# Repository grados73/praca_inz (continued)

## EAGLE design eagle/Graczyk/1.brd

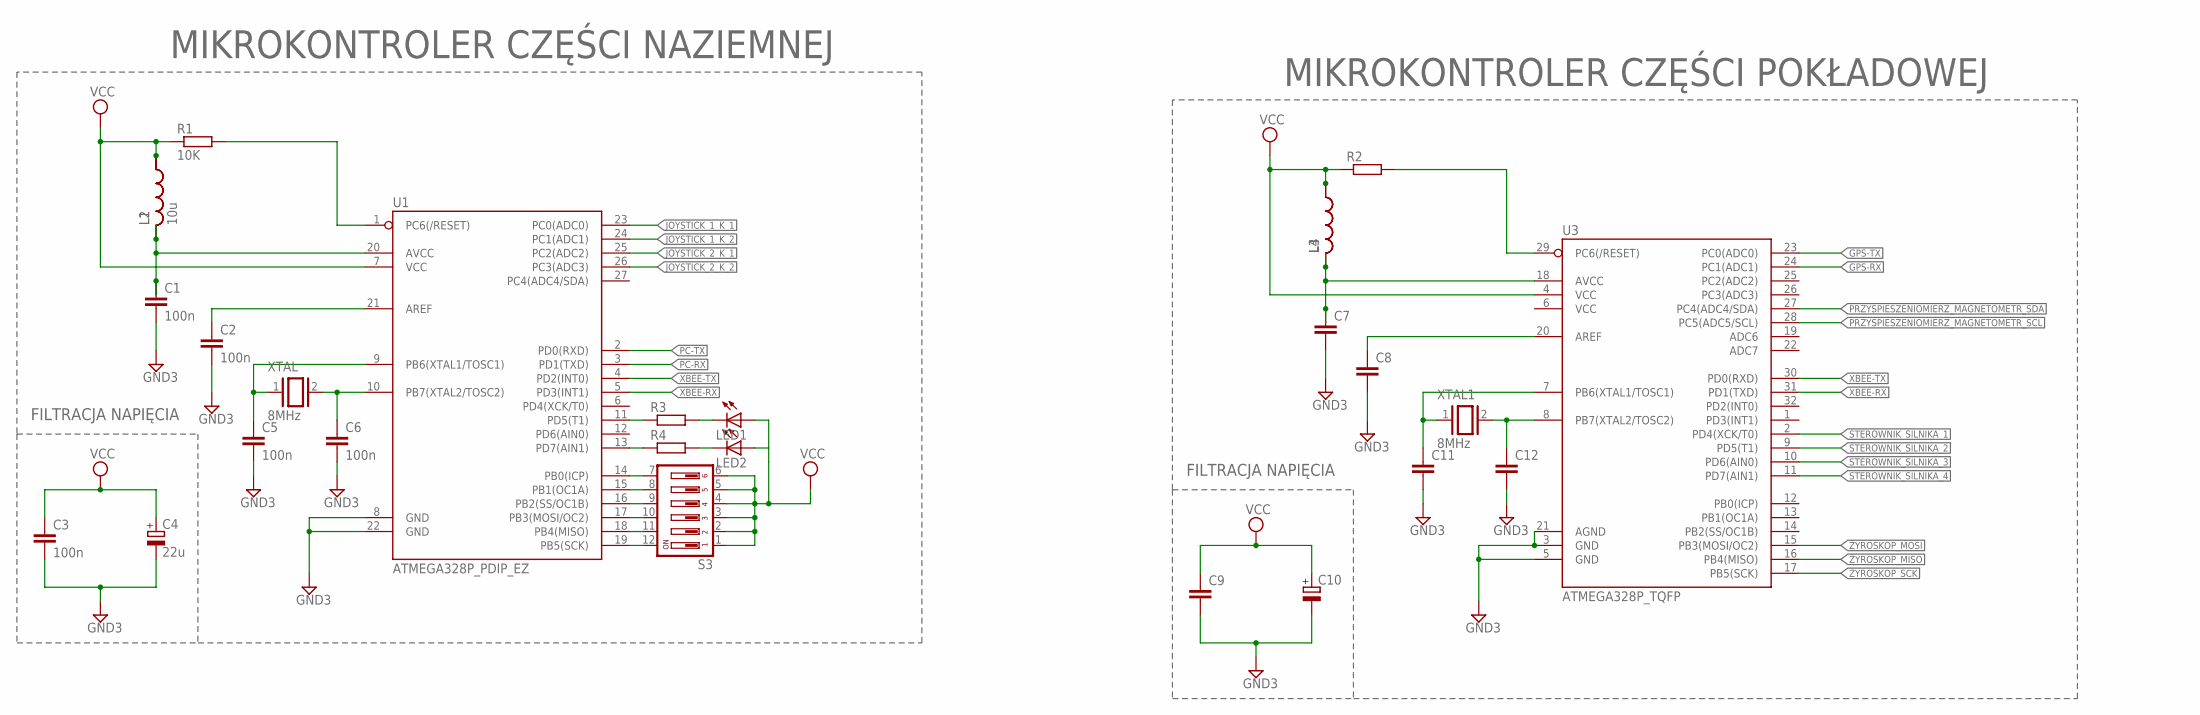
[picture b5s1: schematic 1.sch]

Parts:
C1, C2, C3, C5, C6: 100n; C050-025X075
C4: 22u; B45181A
C7, C8, C9, C11, C12: C-EU050-025X075; C050-025X075
C10: CPOL-EUB45181A; B45181A
L1, L3, L4: L-US0207/10; 0207/10
L2: 10u; 0207/10
LED1, LED2: LEDIRL80A; IRL80A
R1: 10K; 0204/5
R2, R3, R4: R-EU_0204/5; 0204/5
S3: SD4-06
U1: ATMEGA328P_PDIP_EZ; DIP28-SIMON-KIT
U3: ATMEGA328P_TQFP; TQFP32-08
XTAL, XTAL1: 8MHz; Q

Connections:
GND3: C1.2, C2.2, C3.2, C4.-, C5.2, C6.2, C7.2, C8.2, C9.2, C10.-, C11.2, C12.2, U1.8 (GND), U1.22 (GND), U3.3 (GND), U3.5 (GND), U3.21 (AGND)
GPS-RX: U3.24 (PC1(ADC1))
GPS-TX: U3.23 (PC0(ADC0))
JOYSTICK_1_K_1: U1.23 (PC0(ADC0))
JOYSTICK_1_K_2: U1.24 (PC1(ADC1))
JOYSTICK_2_K_1: U1.25 (PC2(ADC2))
JOYSTICK_2_K_2: U1.26 (PC3(ADC3))
unnamed: R1.2, U1.1 (PC6(/RESET))
unnamed: C1.1, L1.2, L2.2, U1.20 (AVCC)
unnamed: C2.1, U1.21 (AREF)
unnamed: R2.2, U3.29 (PC6(/RESET))
unnamed: C6.1, U1.10 (PB7(XTAL2/TOSC2)), XTAL.2
unnamed: C5.1, U1.9 (PB6(XTAL1/TOSC1)), XTAL.1
unnamed: C7.1, L3.2, L4.2, U3.18 (AVCC)
unnamed: C8.1, U3.20 (AREF)
unnamed: C12.1, U3.8 (PB7(XTAL2/TOSC2)), XTAL1.2
unnamed: C11.1, U3.7 (PB6(XTAL1/TOSC1)), XTAL1.1
unnamed: LED1.K (C), R3.2
unnamed: S3.7, U1.14 (PB0(ICP))
unnamed: S3.8, U1.15 (PB1(OC1A))
unnamed: S3.9, U1.16 (PB2(SS/OC1B))
unnamed: S3.10, U1.17 (PB3(MOSI/OC2))
unnamed: S3.11, U1.18 (PB4(MISO))
unnamed: S3.12, U1.19 (PB5(SCK))
unnamed: LED2.K (C), R4.2
unnamed: R4.1, U1.13 (PD7(AIN1))
unnamed: R3.1, U1.11 (PD5(T1))
PRZYSPIESZENIOMIERZ_MAGNETOMETR_SCL: U3.28 (PC5(ADC5/SCL))
PRZYSPIESZENIOMIERZ_MAGNETOMETR_SDA: U3.27 (PC4(ADC4/SDA))
STEROWNIK_SILNIKA_1: U3.2 (PD4(XCK/T0))
STEROWNIK_SILNIKA_2: U3.9 (PD5(T1))
STEROWNIK_SILNIKA_3: U3.10 (PD6(AIN0))
STEROWNIK_SILNIKA_4: U3.11 (PD7(AIN1))
VCC: C3.1, C4.+, C9.1, C10.+, L1.1, L2.1, L3.1, L4.1, LED1.A, LED2.A, R1.1, R2.1, S3.1, S3.2, S3.3, S3.4, S3.5, S3.6, U1.7 (VCC), U3.4 (VCC)
XBEE-RX: U3.31 (PD1(TXD))
XBEE-TX: U3.30 (PD0(RXD))
ŻYROSKOP_MISO: U3.16 (PB4(MISO))
ŻYROSKOP_MOSI: U3.15 (PB3(MOSI/OC2))
ŻYROSKOP_SCK: U3.17 (PB5(SCK))

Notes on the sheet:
MIKROKONTROLER CZĘŚCI NAZIEMNEJ
MIKROKONTROLER CZĘŚCI POKŁADOWEJ
FILTRACJA NAPIĘCIA

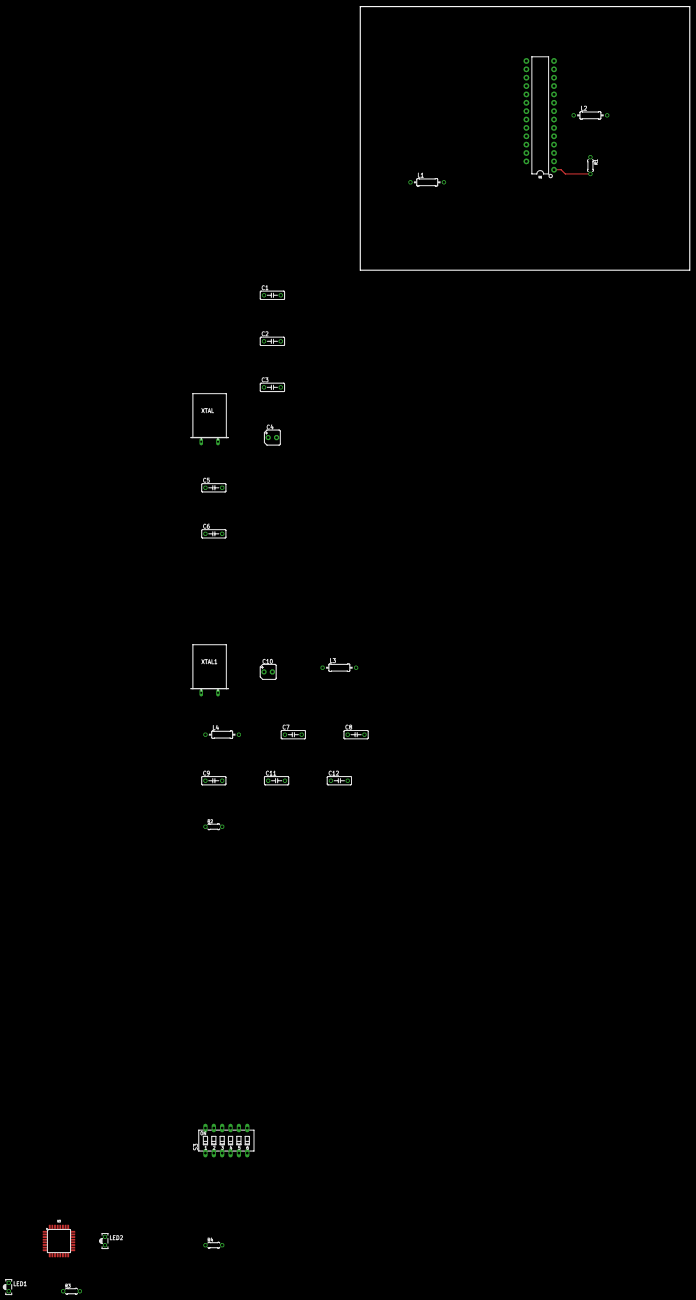
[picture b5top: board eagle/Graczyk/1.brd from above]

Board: 2 copper layers, 100.0 x 80.0 mm, 27 parts (0 on the bottom side), 22 nets.

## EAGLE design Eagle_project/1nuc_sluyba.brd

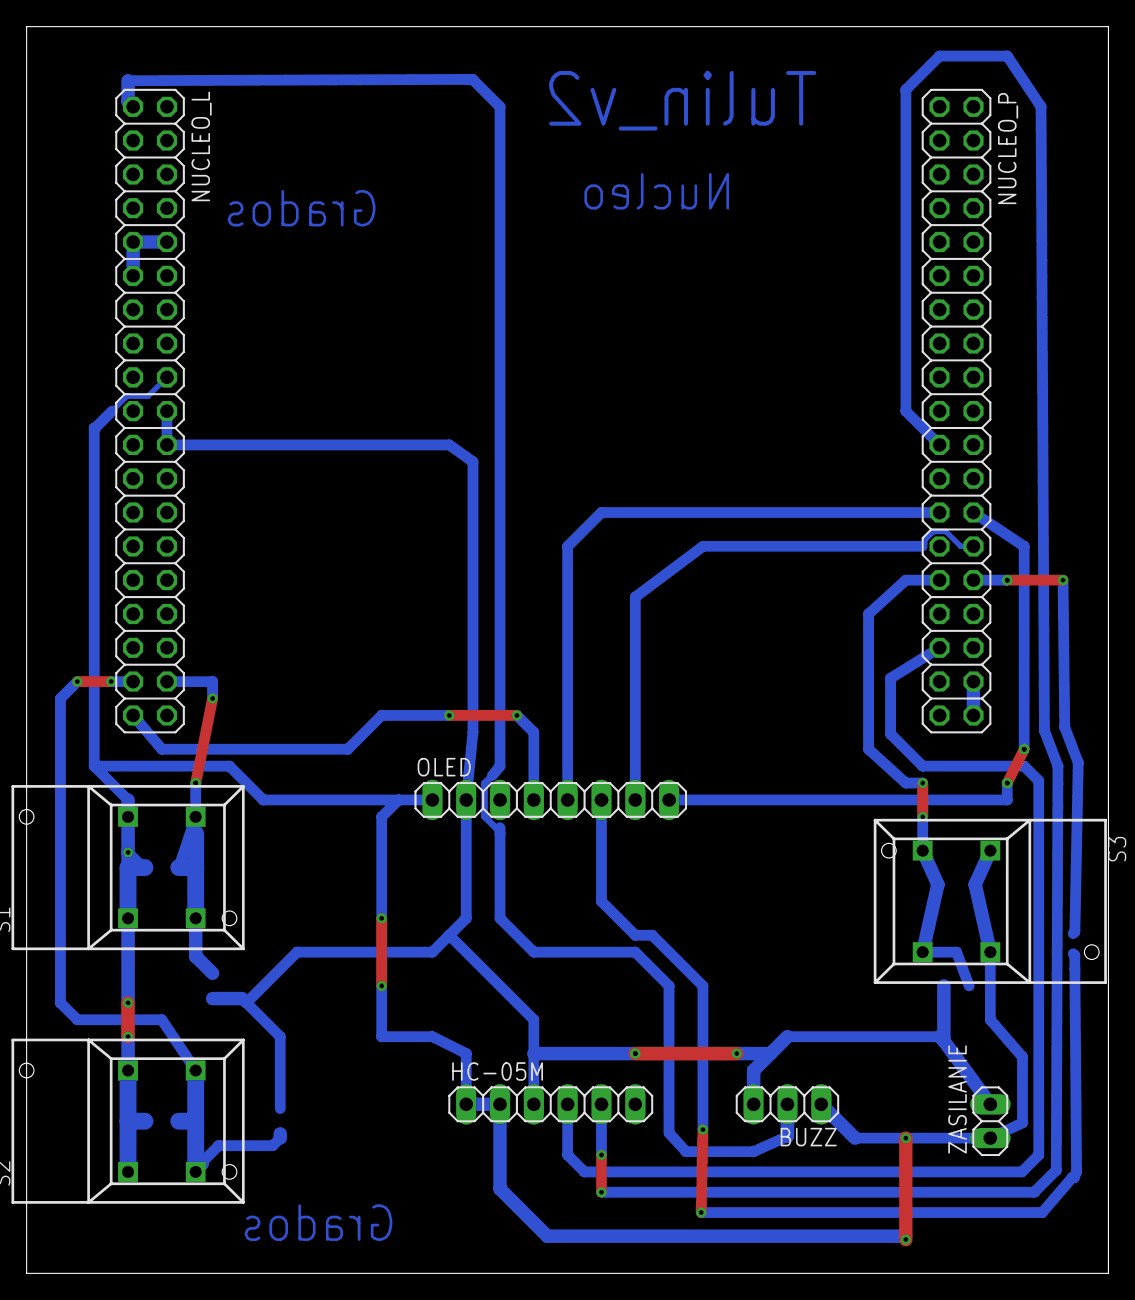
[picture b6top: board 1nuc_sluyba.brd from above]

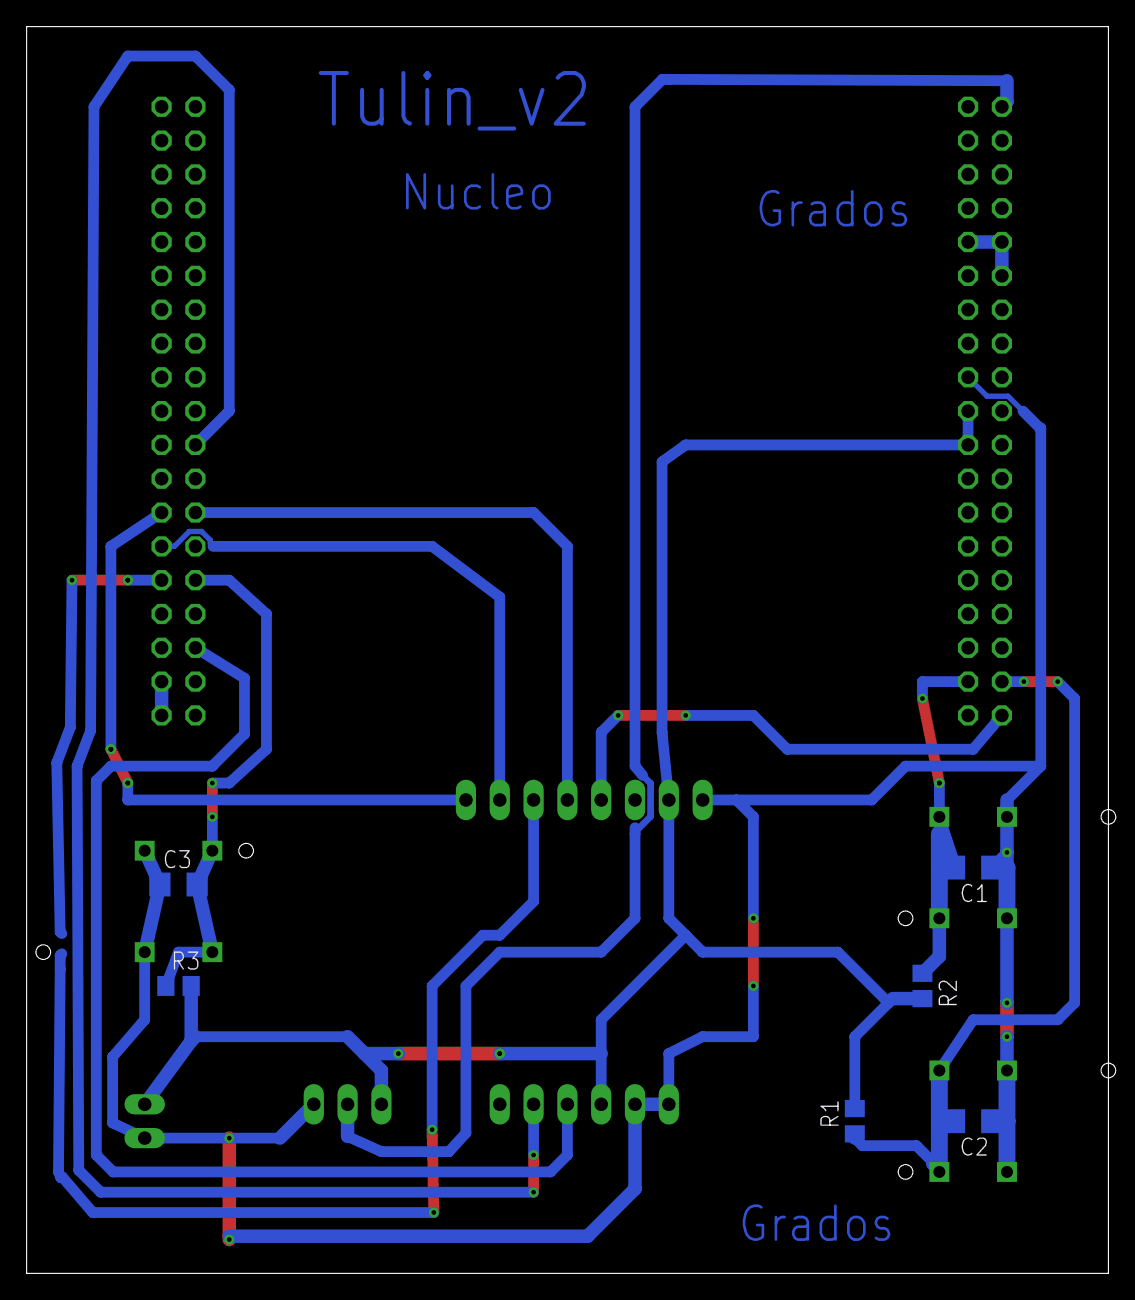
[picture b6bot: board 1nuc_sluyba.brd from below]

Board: 2 copper layers, 81.3 x 93.7 mm, 15 parts (6 on the bottom side), 15 nets.

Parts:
BUZZ: 1X03
C1, C2, C3: 100n; C1206
HC-05M: 1X06
NUCLEO_L: 2X19
NUCLEO_P: 2X19
OLED: 1X08
R1, R2, R3: 100k; R0805
S1, S2, S3: 5501
ZASILANIE: 1X02

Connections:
GND: BUZZ.3, HC-05M.3, NUCLEO_L.20, NUCLEO_L.22, OLED.2, R1.2, R2.2, R3.2, ZASILANIE.2
NC: NUCLEO_L.9, NUCLEO_L.10, NUCLEO_L.11, NUCLEO_L.26
NCC: NUCLEO_P.36, NUCLEO_P.38
PA9: HC-05M.5, NUCLEO_P.21
PA10: HC-05M.4, NUCLEO_P.33
PB5: C3.2, NUCLEO_P.29, R3.1, S3.NC, S3.NO
PB10: NUCLEO_P.25, OLED.5
PB13: NUCLEO_P.30, OLED.6
PB14: NUCLEO_P.28, OLED.7
PB15: NUCLEO_P.26, OLED.8
PC1: C1.2, NUCLEO_L.36, R2.1, S1.NC, S1.NO
PC2: C2.2, NUCLEO_L.35, R1.1, S2.NC, S2.NO
PC3: NUCLEO_L.37, OLED.4
PC10: BUZZ.2, NUCLEO_L.1
VCC: BUZZ.1, C1.1, C2.1, C3.1, HC-05M.1, HC-05M.2, NUCLEO_L.18, OLED.1, S1.1A, S1.1B, S2.1A, S2.1B, S3.1A, S3.1B, ZASILANIE.1

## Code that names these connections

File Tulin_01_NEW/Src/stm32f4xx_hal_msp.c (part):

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    __HAL_RCC_ADC1_CLK_ENABLE();
  
    /**ADC1 GPIO Configuration    
    PA1     ------> ADC1_IN1
    PA2     ------> ADC1_IN2
    PA3     ------> ADC1_IN3
    PB0     ------> ADC1_IN8
    PB1     ------> ADC1_IN9 
    */
    GPIO_InitStruct.Pin = GPIO_PIN_1|GPIO_PIN_2|GPIO_PIN_3;
    GPIO_InitStruct.Mode = GPIO_MODE_ANALOG;
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    __HAL_RCC_ADC1_CLK_DISABLE();
  
    /**ADC1 GPIO Configuration    
    PA1     ------> ADC1_IN1
    PA2     ------> ADC1_IN2
    PA3     ------> ADC1_IN3
    PB0     ------> ADC1_IN8
    PB1     ------> ADC1_IN9 
    */
    HAL_GPIO_DeInit(GPIOA, GPIO_PIN_1|GPIO_PIN_2|GPIO_PIN_3);

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
  /* USER CODE END TIM2_MspPostInit 0 */
    /**TIM2 GPIO Configuration    
    PA15     ------> TIM2_CH1 
    */
    GPIO_InitStruct.Pin = GPIO_PIN_15;
    GPIO_InitStruct.Mode = GPIO_MODE_AF_PP;
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  /* USER CODE END TIM3_MspPostInit 0 */
  
    /**TIM3 GPIO Configuration    
    PC6     ------> TIM3_CH1 
    */
    GPIO_InitStruct.Pin = GPIO_PIN_6;
    GPIO_InitStruct.Mode = GPIO_MODE_AF_PP;
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    __HAL_RCC_USART1_CLK_ENABLE();
  
    /**USART1 GPIO Configuration    
    PB6     ------> USART1_TX
    PB7     ------> USART1_RX 
    */
    GPIO_InitStruct.Pin = GPIO_PIN_6|GPIO_PIN_7;
    GPIO_InitStruct.Mode = GPIO_MODE_AF_PP;
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    __HAL_RCC_USART1_CLK_DISABLE();
  
    /**USART1 GPIO Configuration    
    PB6     ------> USART1_TX
    PB7     ------> USART1_RX 
    */
    HAL_GPIO_DeInit(GPIOB, GPIO_PIN_6|GPIO_PIN_7);

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
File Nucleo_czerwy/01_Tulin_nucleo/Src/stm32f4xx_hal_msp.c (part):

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    __HAL_RCC_ADC1_CLK_ENABLE();
  
    /**ADC1 GPIO Configuration    
    PA1     ------> ADC1_IN1 
    */
    GPIO_InitStruct.Pin = GPIO_PIN_1;
    GPIO_InitStruct.Mode = GPIO_MODE_ANALOG;
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    __HAL_RCC_ADC1_CLK_DISABLE();
  
    /**ADC1 GPIO Configuration    
    PA1     ------> ADC1_IN1 
    */
    HAL_GPIO_DeInit(GPIOA, GPIO_PIN_1);

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    __HAL_RCC_SPI2_CLK_ENABLE();
  
    /**SPI2 GPIO Configuration    
    PC3     ------> SPI2_MOSI
    PB10     ------> SPI2_SCK 
    */
    GPIO_InitStruct.Pin = MOSI_Pin;
    GPIO_InitStruct.Mode = GPIO_MODE_AF_PP;
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    __HAL_RCC_SPI2_CLK_DISABLE();
  
    /**SPI2 GPIO Configuration    
    PC3     ------> SPI2_MOSI
    PB10     ------> SPI2_SCK 
    */
    HAL_GPIO_DeInit(MOSI_GPIO_Port, MOSI_Pin);

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    __HAL_RCC_USART1_CLK_ENABLE();
  
    /**USART1 GPIO Configuration    
    PA9     ------> USART1_TX
    PA10     ------> USART1_RX 
    */
    GPIO_InitStruct.Pin = GPIO_PIN_9|GPIO_PIN_10;
    GPIO_InitStruct.Mode = GPIO_MODE_AF_PP;
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    __HAL_RCC_USART1_CLK_DISABLE();
  
    /**USART1 GPIO Configuration    
    PA9     ------> USART1_TX
    PA10     ------> USART1_RX 
    */
    HAL_GPIO_DeInit(GPIOA, GPIO_PIN_9|GPIO_PIN_10);

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
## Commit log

2020-10-10 wersja (nie) finalna pracy
2021-01-21 Nucleo_code
2021-01-21 pcb projects
2021-01-21 wersja finalna kodu na disco
2021-01-21 Wersja finalna kodu na nucleo
2021-01-21 Zdjęcia oraz schematy blokowe
2021-02-09 Dodane zdjęcia i schematy blokowe.
